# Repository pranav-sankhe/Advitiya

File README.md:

# Advitiya| Electrical Subsystem| [Pranav Sankhe](https://sabsathai.github.io/)

Hey! I am 3rd year Undergraduate at Electrical Engineering, IIT Bombay and a core member of [Electrical Subsystem](http://www.aero.iitb.ac.in/pratham/elecSS.php) of [Student Satellite Team, IIT Bombay](http://www.aero.iitb.ac.in/pratham/). **Advitiya** is the 2nd student satellite of IITB, technically advanced and efficient version of the 1st, Pratham. 

This is my repository where I maintain my codes related to Advitiya. 

</br>

If you want to contribute, you are most welcome :smiley: .Feel free to send a [pull request](https://help.github.com/articles/creating-a-pull-request/)

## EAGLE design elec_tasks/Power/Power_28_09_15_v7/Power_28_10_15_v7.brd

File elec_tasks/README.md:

# Electrical Subsystem Tasks

This contains the collection of all the codes written for tasks of electrical subsystem of Advitiya

- **Power** 
	Analysing the power boards of Pratham

- **Insystem Programming**
	The tasks involves programming a Atmega using another Atmega. 

- **UART Interrupts** 
	This task involved reading up on UART Transmit Interrupts and what specific applications do they cover

- **WatchDog Timer** 
	An implementation of WatchDog Timer in an Embedded System

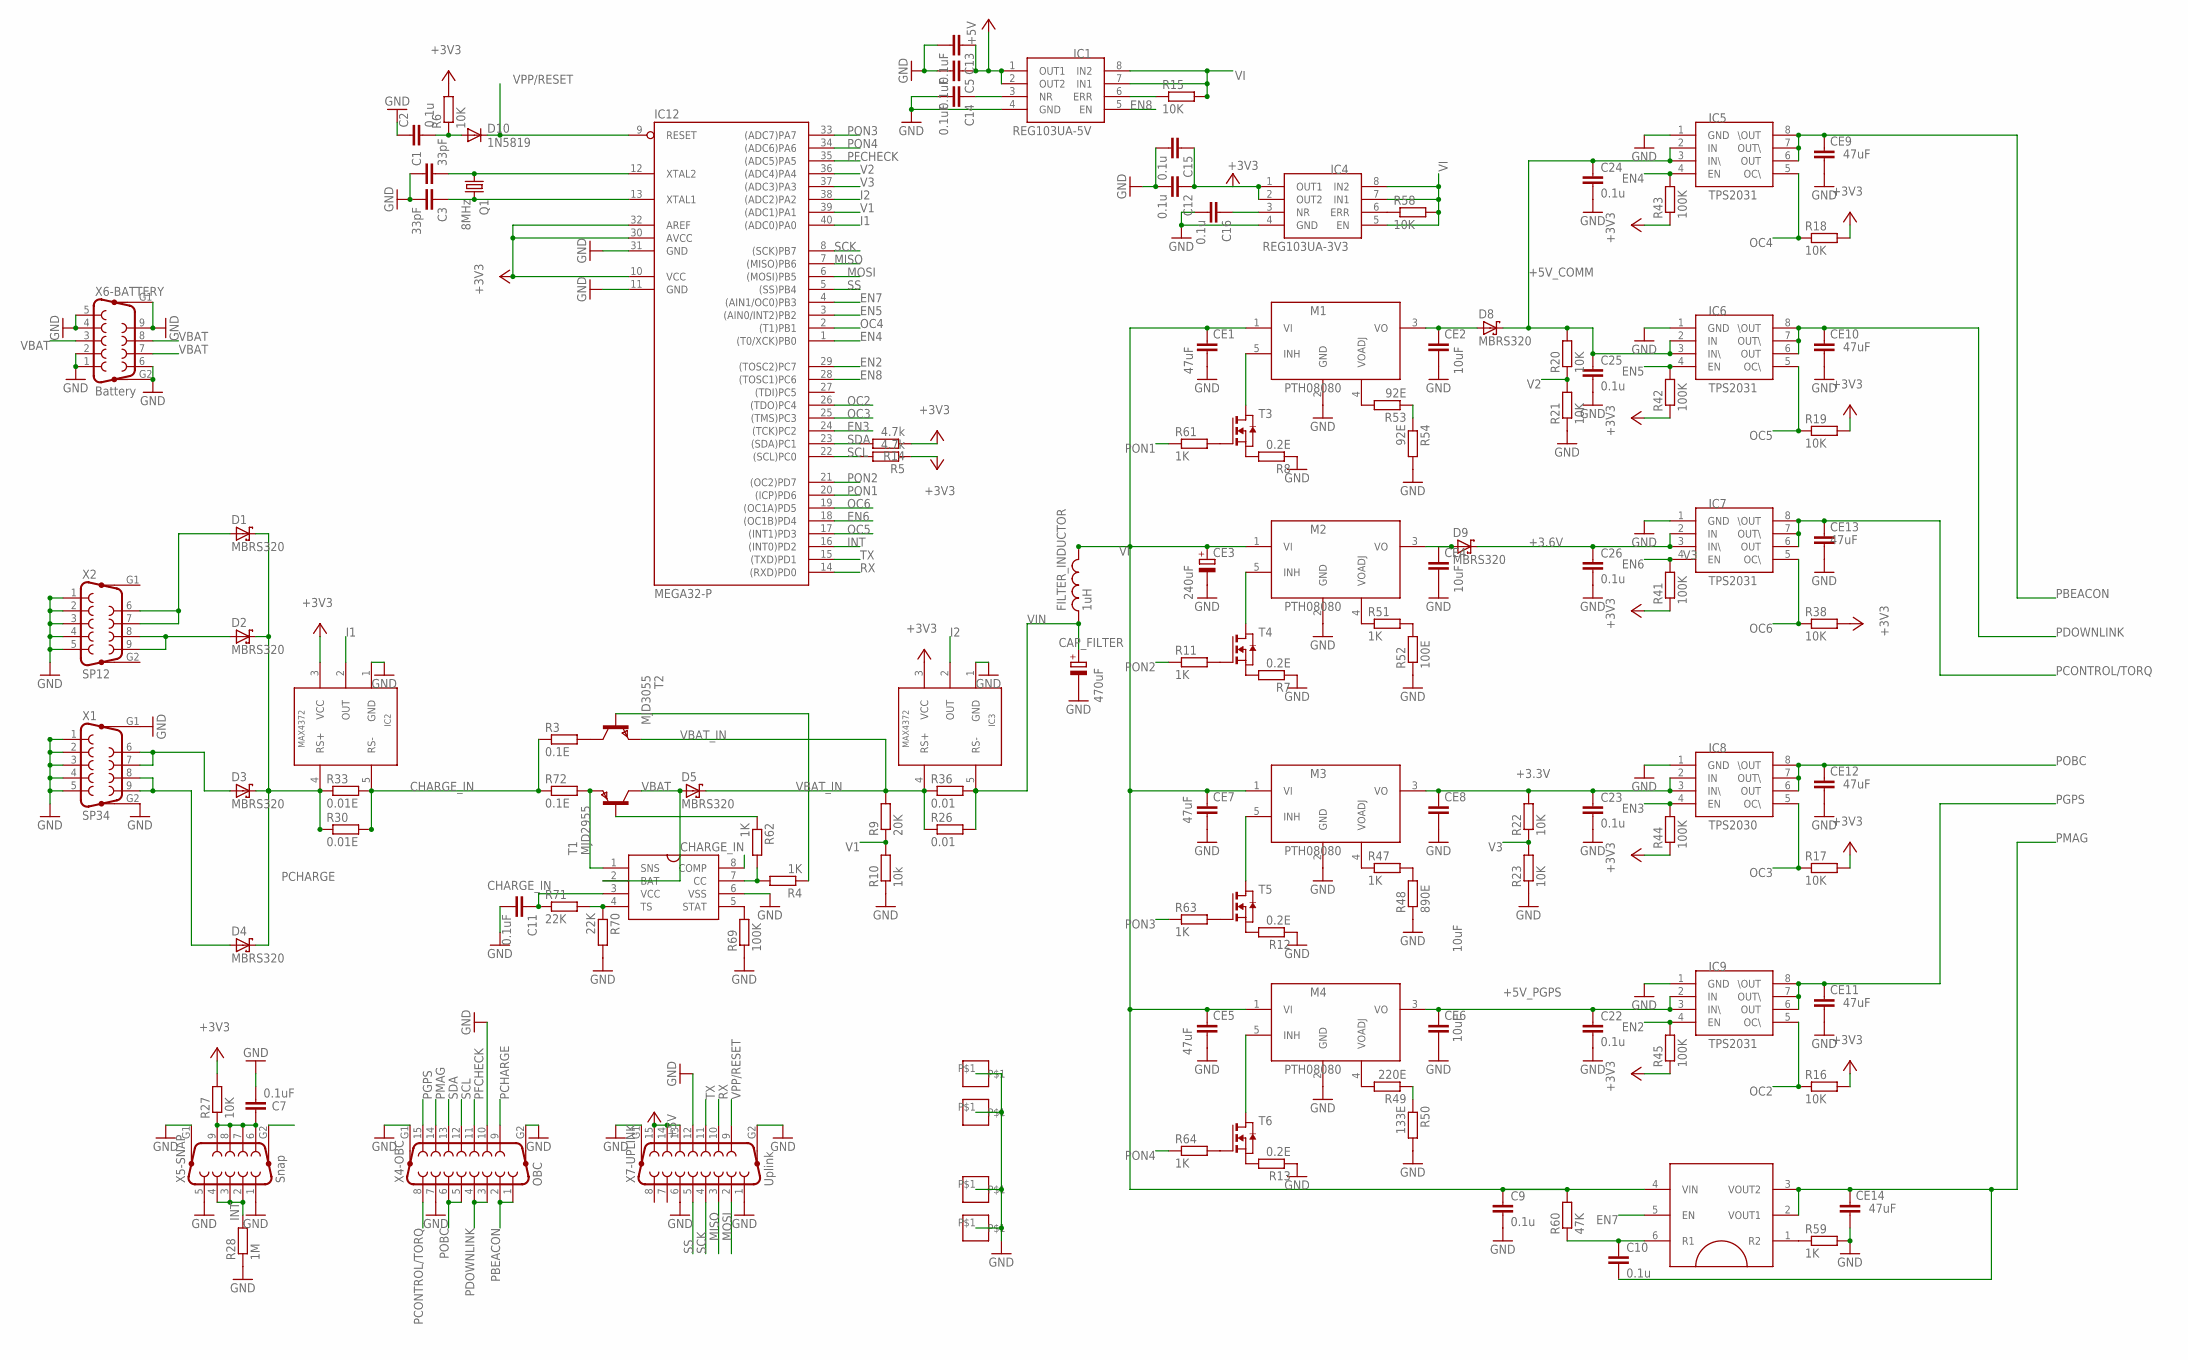
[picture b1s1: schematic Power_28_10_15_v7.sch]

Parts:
C1, C3: 33pF; C1206
C2, C9, C10, C12, C15, C16, C22, C23, C24, C25, C26: 0.1u; C1206
C5, C7, C11, C13, C14: 0.1uF; C1206
CAP_FILTER: 470uF; CAP-POL-T3
CE1, CE5, CE7, CE9, CE10, CE11, CE12, CE13, CE14: 47uF; C1206K
CE2, CE4, CE6, CE8: 10uF; C1206K
CE3: 240uF; CAP-POL-T2
D1, D2, D3, D4, D5, D8, D9: MBRS320; DIODE
D10: 1N5819; D-5
FILTER_INDUCTOR: 1uH; MSS1260
IC1: REG103UA-5V; SO8
IC2, IC3: MAX4372; SOT-23-5
IC4: REG103UA-3V3; SO8
IC5, IC6, IC7, IC9: TPS2031; SO-8
IC8: TPS2030; SO-8
IC10: FDC6324; SUPER-SOT-6
IC11: BO2057; SOIC-8
IC12: MEGA32-P; DIL40
M1, M2, M3, M4: PTH08080; DIP-05
Q1: 8MHz; HC49/S
R3, R72: 0.1E; R1206
R4, R11, R47, R51, R59, R61, R62, R63, R64: 1K; R1206
R5, R14: 4.7k; R1206
R6, R15, R16, R17, R18, R19, R20, R21, R22, R23, R27, R38, R58: 10K; R1206
R7, R8, R12, R13: 0.2E; R1206
R9: 20K; R1206
R10: 10k; R1206
R26, R36: 0.01; R1206
R28: 1M; R1206
R30, R33: 0.01E; R1206
R41, R42, R43, R44, R45, R69: 100K; R1206
R48: 890E; R1206
R49: 220E; R1206
R50: 133E; R1206
R52: 100E; R1206
R53, R54: 92E; R1206
R60: 47K; R1206
R70, R71: 22K; R1206
T1: MJD2955; DPAK-TO252
T2: MJD3055; DPAK-TO252
T3, T4, T5, T6: NMOSSOT23; SOT-23
U$4, U$16, U$18, U$19: MOUNT_SQ; MOUNT_10MM
X1: SP34; F09HP
X2: SP12; F09HP
X4-OBC: OBC; F15HP
X5-SNAP: Snap; F09HP
X6-BATTERY: Battery; F09HP
X7-UPLINK: Uplink; F15HP

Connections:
+3.3V: C23.1, CE8.1, IC8.2 (IN), IC8.3 (IN\), M3.3 (VO), R22.2
+3.6V: C26.1, D9.C, IC7.2 (IN), IC7.3 (IN\)
+3V3: C12.1, C15.1, IC2.3 (VCC), IC3.3 (VCC), IC4.1 (OUT1), IC4.2 (OUT2), IC12.10 (VCC), IC12.30 (AVCC), IC12.32 (AREF), R5.1, R6.2, R14.1, R16.2, R17.2, R18.2, R19.2, R27.2, R38.2, R41.1, R42.1, R43.1, R44.1, R45.1
+5V: C5.1, C13.1, IC1.1 (OUT1), IC1.2 (OUT2), X7-UPLINK.13, X7-UPLINK.14, X7-UPLINK.15
+5V_COMM: C24.1, C25.1, D8.C, IC5.2 (IN), IC5.3 (IN\), IC6.2 (IN), IC6.3 (IN\), R20.2
+5V_PGPS: C22.1, CE6.1, IC9.2 (IN), IC9.3 (IN\), M4.3 (VO)
CHARGE_IN: C11.1, IC2.5 (RS-), IC11.3 (VCC), IC11.8 (COMP), R3.1, R30.2, R33.2, R71.1, R72.1
EN2: IC9.4 (EN), IC12.29 ((TOSC2)PC7), R45.2
EN3: IC8.4 (EN), IC12.24 ((TCK)PC2), R44.2
EN4: IC5.4 (EN), IC12.1 ((T0/XCK)PB0), R43.2
EN5: IC6.4 (EN), IC12.3 ((AIN0/INT2)PB2), R42.2
EN6: IC7.4 (EN), IC12.18 ((OC1B)PD4), R41.2
EN7: IC10.5 (EN), IC12.4 ((AIN1/OC0)PB3)
EN8: IC1.5 (EN), IC12.28 ((TOSC1)PC6)
GND: C1.1, C2.1, C3.2, C5.2, C7.2, C9.2, C11.2, C12.2, C13.2, C14.2, C15.2, C16.2, C22.2, C23.2, C24.2, C25.2, C26.2, CAP_FILTER.P$2 (-), CE1.2, CE2.2, CE3.P$2 (-), CE4.2, CE5.2, CE6.2, CE7.2, CE8.2, CE9.2, CE10.2, CE11.2, CE12.2, CE13.2, CE14.2, IC1.4 (GND), IC2.1 (GND), IC3.1 (GND), IC4.4 (GND), IC5.1 (GND), IC6.1 (GND), IC7.1 (GND), IC8.1 (GND), IC9.1 (GND), IC11.6 (VSS), IC12.11 (GND), IC12.31 (GND), M1.2 (GND), M2.2 (GND), M3.2 (GND), M4.2 (GND), R7.1, R8.1, R10.1, R12.1, R13.1, R21.1, R23.1, R28.1, R48.1, R50.2, R52.1, R54.2, R59.2, R69.1, R70.2, U$4.P$1, U$16.P$1, U$18.P$1, U$19.P$1, X1.1, X1.2, X1.3, X1.4, X1.5, X1.G1, X1.G2, X2.1, X2.2, X2.3, X2.4, X2.5, X4-OBC.7, X4-OBC.10, X4-OBC.G1, X4-OBC.G2, X5-SNAP.1, X5-SNAP.5, X5-SNAP.G1, X5-SNAP.G2, X6-BATTERY.1, X6-BATTERY.2, X6-BATTERY.4, X6-BATTERY.5, X6-BATTERY.6, X6-BATTERY.9, X6-BATTERY.G1, X6-BATTERY.G2, X7-UPLINK.1, X7-UPLINK.6, X7-UPLINK.12, X7-UPLINK.G1, X7-UPLINK.G2
I1: IC2.2 (OUT), IC12.40 ((ADC0)PA0)
I2: IC3.2 (OUT), IC12.38 ((ADC2)PA2)
INT: IC12.16 ((INT0)PD2), R28.2, X5-SNAP.2, X5-SNAP.3, X5-SNAP.4
MISO: IC12.7 ((MISO)PB6), X7-UPLINK.3
MOSI: IC12.6 ((MOSI)PB5), X7-UPLINK.2
unnamed: D3.A, X1.6, X1.7
unnamed: D2.A, X2.8, X2.9
unnamed: C7.1, R27.1, X5-SNAP.6, X5-SNAP.7, X5-SNAP.8, X5-SNAP.9
unnamed: C16.1, IC4.3 (NR)
unnamed: C14.1, IC1.3 (NR)
unnamed: C2.2, D10.A, R6.1
unnamed: IC4.6 (ERR), R58.1
unnamed: R3.2, T2.2 (C)
unnamed: CE2.1, D8.A, M1.3 (VO)
unnamed: CE4.1, D9.A, M2.3 (VO)
unnamed: R4.1, T2.1 (B)
unnamed: C10.1, IC10.6 (R1), R60.1
unnamed: IC1.6 (ERR), R15.1
unnamed: M1.5 (INH), T3.1 (D)
unnamed: M3.5 (INH), T5.1 (D)
unnamed: M4.5 (INH), T6.1 (D)
unnamed: R7.2, T4.2 (S)
unnamed: C3.1, IC12.13 (XTAL1), Q1.2
unnamed: R61.2, T3.3 (G)
unnamed: R8.2, T3.2 (S)
unnamed: R11.2, T4.3 (G)
unnamed: D4.A, X1.8, X1.9
unnamed: IC10.1 (R2), R59.1
unnamed: C1.2, IC12.12 (XTAL2), Q1.1
unnamed: R63.2, T5.3 (G)
unnamed: R12.2, T5.2 (S)
unnamed: R64.2, T6.3 (G)
unnamed: R13.2, T6.2 (S)
unnamed: M2.5 (INH), T4.1 (D)
unnamed: D1.A, X2.6, X2.7
unnamed: M3.4 (VOADJ), R47.1
unnamed: R47.2, R48.2
unnamed: M4.4 (VOADJ), R49.2
unnamed: R49.1, R50.1
unnamed: M2.4 (VOADJ), R51.1
unnamed: R51.2, R52.2
unnamed: M1.4 (VOADJ), R53.2
unnamed: R53.1, R54.1
unnamed: R62.1, T1.1 (B)
unnamed: IC11.5 (STAT), R69.2
unnamed: IC11.4 (TS), R70.1, R71.2
unnamed: IC11.1 (SNS), R72.2, T1.3 (E)
unnamed: IC11.7 (CC), R4.2, R62.2
OC2: IC9.5 (OC\), IC12.26 ((TDO)PC4), R16.1
OC3: IC8.5 (OC\), IC12.25 ((TMS)PC3), R17.1
OC4: IC5.5 (OC\), IC12.2 ((T1)PB1), R18.1
OC5: IC6.5 (OC\), IC12.17 ((INT1)PD3), R19.1
OC6: IC7.5 (OC\), IC12.19 ((OC1A)PD5), R38.1
PBEACON: CE9.1, IC5.6 (OUT), IC5.7 (OUT\), IC5.8 (\OUT), X4-OBC.1, X4-OBC.2
PCHARGE: D1.C, D2.C, D3.C, D4.C, IC2.4 (RS+), R30.1, R33.1, X4-OBC.9
PCONTROL/TORQ: CE13.1, IC7.6 (OUT), IC7.7 (OUT\), IC7.8 (\OUT), X4-OBC.8
PDOWNLINK: CE10.1, IC6.6 (OUT), IC6.7 (OUT\), IC6.8 (\OUT), X4-OBC.3, X4-OBC.4
PFCHECK: IC12.35 ((ADC5)PA5), X4-OBC.11
PGPS: CE11.1, IC9.6 (OUT), IC9.7 (OUT\), IC9.8 (\OUT), X4-OBC.15
PMAG: C10.2, CE14.1, IC10.2 (VOUT1), IC10.3 (VOUT2), X4-OBC.14
POBC: CE12.1, IC8.6 (OUT), IC8.7 (OUT\), IC8.8 (\OUT), X4-OBC.5, X4-OBC.6
PON1: IC12.20 ((ICP)PD6), R61.1
PON2: IC12.21 ((OC2)PD7), R11.1
PON3: IC12.33 ((ADC7)PA7), R63.1
PON4: IC12.34 ((ADC6)PA6), R64.1
RX: IC12.14 ((RXD)PD0), X7-UPLINK.10
SCK: IC12.8 ((SCK)PB7), X7-UPLINK.4
SCL: IC12.22 ((SCL)PC0), R5.2, X4-OBC.12
SDA: IC12.23 ((SDA)PC1), R14.2, X4-OBC.13
SS: IC12.5 ((SS)PB4), X7-UPLINK.5
TX: IC12.15 ((TXD)PD1), X7-UPLINK.11
V1: IC12.39 ((ADC1)PA1), R9.1, R10.2
V2: IC12.36 ((ADC4)PA4), R20.1, R21.2
V3: IC12.37 ((ADC3)PA3), R22.1, R23.2
VBAT: D5.A, IC11.2 (BAT), T1.2 (C), X6-BATTERY.3, X6-BATTERY.7, X6-BATTERY.8
VBAT_IN: D5.C, IC3.4 (RS+), R9.2, R26.1, R36.1, T2.3 (E)
VI: C9.1, CE1.1, CE3.P$1 (+), CE5.1, CE7.1, FILTER_INDUCTOR.P$1, IC1.7 (IN1), IC1.8 (IN2), IC4.5 (EN), IC4.7 (IN1), IC4.8 (IN2), IC10.4 (VIN), M1.1 (VI), M2.1 (VI), M3.1 (VI), M4.1 (VI), R15.2, R58.2, R60.2
VIN: CAP_FILTER.P$1 (+), FILTER_INDUCTOR.P$2, IC3.5 (RS-), R26.2, R36.2
VPP/RESET: D10.C, IC12.9 (RESET), X7-UPLINK.9

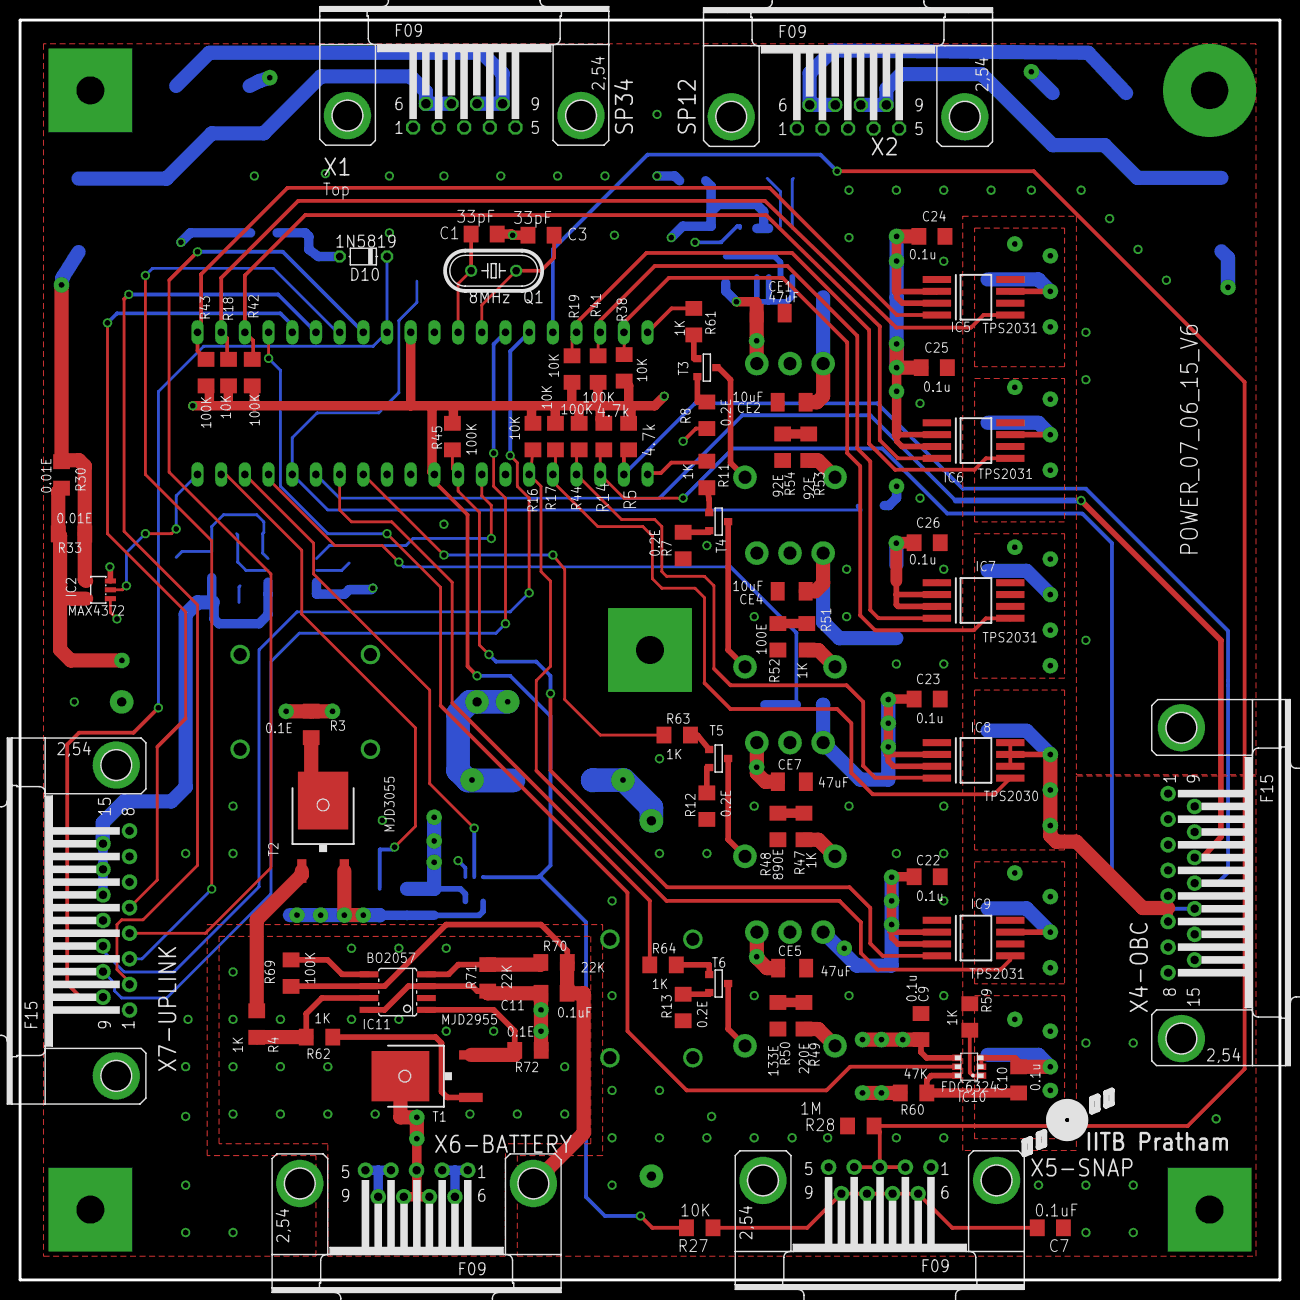
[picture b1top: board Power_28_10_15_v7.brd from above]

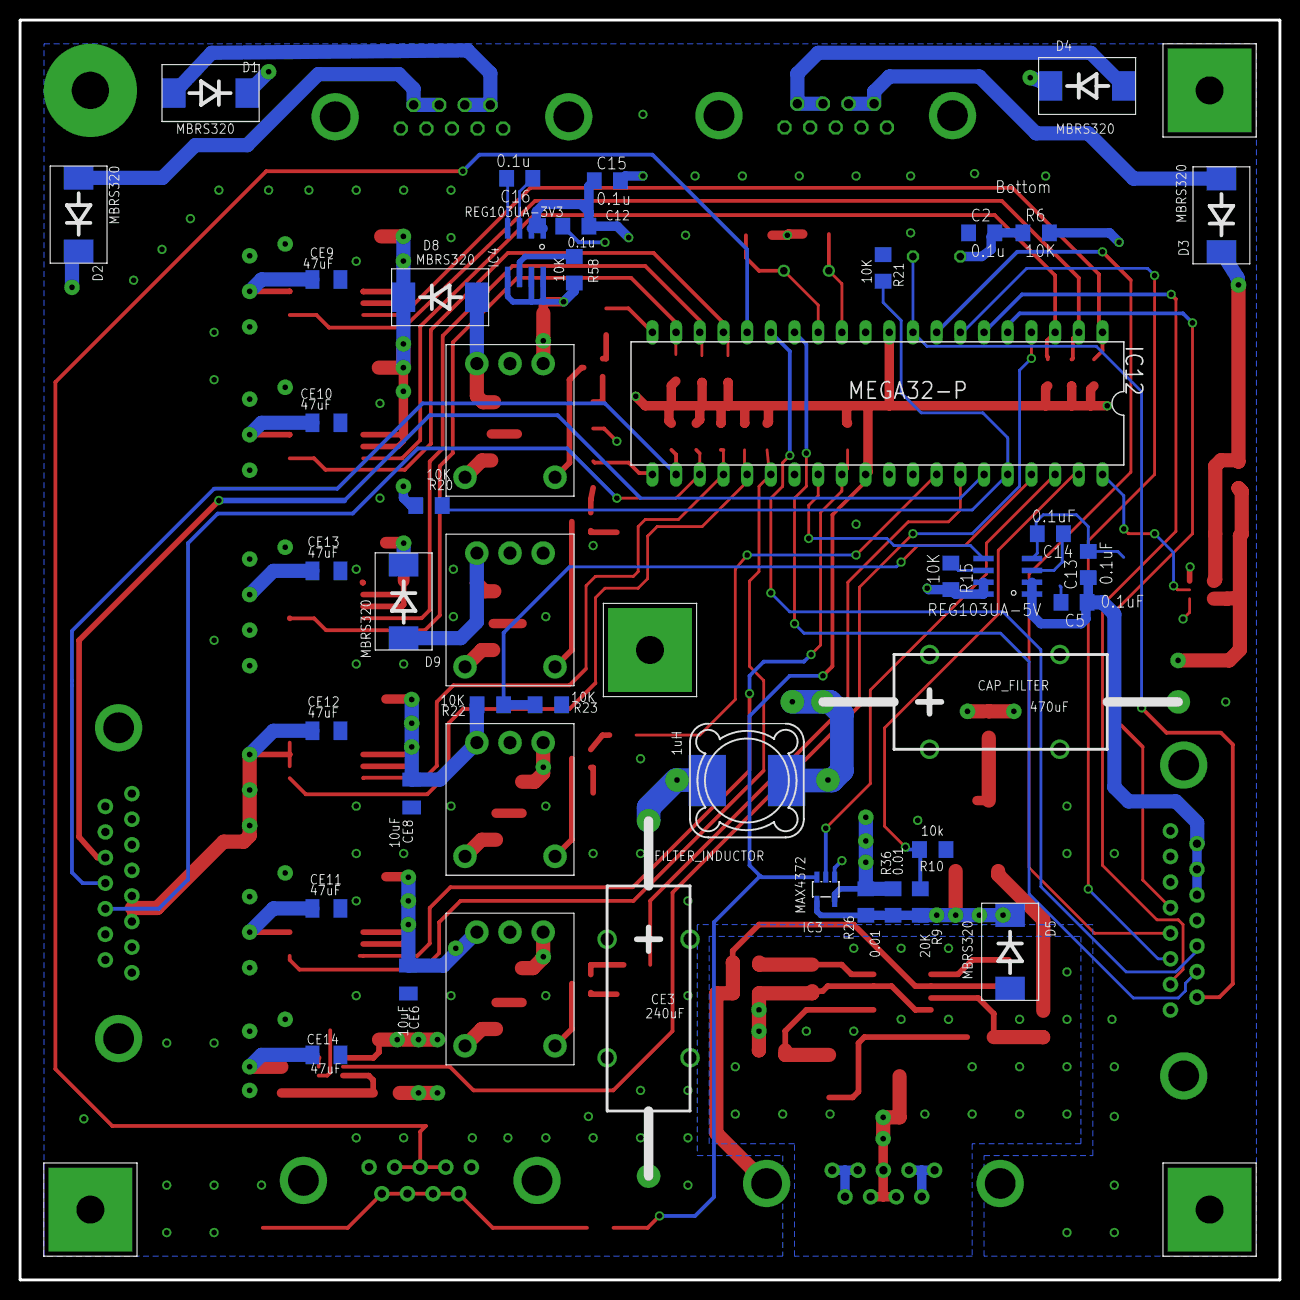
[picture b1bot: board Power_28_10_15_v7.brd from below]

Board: 2 copper layers, 135.1 x 135.1 mm, 127 parts (48 on the bottom side), 94 nets.

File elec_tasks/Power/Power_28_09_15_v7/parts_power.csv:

C2,0.1u,C1206,rcl
C9,0.1u,C1206,rcl
C10,0.1u,C1206,rcl
C12,0.1u,C1206,rcl
C15,0.1u,C1206,rcl
C16,0.1u,C1206,rcl
C22,0.1u,C1206,rcl
C23,0.1u,C1206,rcl
C24,0.1u,C1206,rcl
C25,0.1u,C1206,rcl
C26,0.1u,C1206,rcl
C5,0.1uF,C1206,rcl
C7,0.1uF,C1206,rcl
C11,0.1uF,C1206,rcl
C13,0.1uF,C1206,rcl
C14,0.1uF,C1206,rcl
C1,33pF,C1206,rcl
C3,33pF,C1206,rcl
CE2,10uF,C1206K,rcl
CE4,10uF,C1206K,rcl
CE6,10uF,C1206K,rcl
CE8,10uF,C1206K,rcl
CE1,47uF,C1206K,rcl
CE5,47uF,C1206K,rcl
CE7,47uF,C1206K,rcl
CE9,47uF,C1206K,rcl
CE10,47uF,C1206K,rcl
CE11,47uF,C1206K,rcl
CE12,47uF,C1206K,rcl
CE13,47uF,C1206K,rcl
CE14,47uF,C1206K,rcl
CE3,240uF,CAP-POL-T2,satellite
CAP_FILTER,470uF,CAP-POL-T3,satellite
D10,1N5819,D-5,diode
IC12,MEGA32-P,DIL40,atmel
D1,MBRS320,DIODE,satellite
D2,MBRS320,DIODE,satellite
D3,MBRS320,DIODE,satellite
D4,MBRS320,DIODE,satellite
D5,MBRS320,DIODE,satellite
D8,MBRS320,DIODE,satellite
D9,MBRS320,DIODE,satellite
M1,PTH08080,DIP-05,satellite
M2,PTH08080,DIP-05,satellite
M3,PTH08080,DIP-05,satellite
M4,PTH08080,DIP-05,satellite
T1,MJD2955,DPAK-TO252,satellite
T2,MJD3055,DPAK-TO252,satellite
X6-BATTERY,Battery,F09HP,satellite
X5-SNAP,Snap,F09HP,satellite
X2,SP12,F09HP,con-subd
X1,SP34,F09HP,con-subd
X4-OBC,OBC,F15HP,satellite
X7-UPLINK,Uplink,F15HP,satellite
Q1,8MHz,HC49/S,crystal
U$4,MOUNT_SQ,MOUNT_10MM,satellite
U$16,MOUNT_SQ,MOUNT_10MM,satellite
U$18,MOUNT_SQ,MOUNT_10MM,satellite
U$19,MOUNT_SQ,MOUNT_10MM,satellite
FILTER_INDUCT,OR 1uH,MSS1260,inductor-coilcraft(2)
R26,0.01,R1206,rcl
R36,0.01,R1206,rcl
R30,0.01E,R1206,rcl
R33,0.01E,R1206,rcl
R3,0.1E,R1206,rcl
R72,0.1E,R1206,rcl
R7,0.2E,R1206,rcl
R8,0.2E,R1206,rcl
R12,0.2E,R1206,rcl
R13,0.2E,R1206,rcl
R52,100E,R1206,rcl
R41,100K,R1206,rcl
R42,100K,R1206,rcl
R43,100K,R1206,rcl
R44,100K,R1206,rcl
R45,100K,R1206,rcl
R69,100K,R1206,rcl
R6,10K,R1206,rcl
R10,10k,R1206,rcl
R15,10K,R1206,rcl
R16,10K,R1206,rcl
R17,10K,R1206,rcl
R18,10K,R1206,rcl
R19,10K,R1206,rcl
R20,10K,R1206,rcl
R21,10K,R1206,rcl
R22,10K,R1206,rcl
R23,10K,R1206,rcl
R27,10K,R1206,rcl
R38,10K,R1206,rcl
R58,10K,R1206,rcl
R50,133E,R1206,rcl
R4,1K,R1206,rcl
R11,1K,R1206,rcl
R47,1K,R1206,rcl
R51,1K,R1206,rcl
R59,1K,R1206,rcl
R61,1K,R1206,rcl
R62,1K,R1206,rcl
R63,1K,R1206,rcl
R64,1K,R1206,rcl
R28,1M,R1206,rcl
R9,20K,R1206,rcl
R49,220E,R1206,rcl
R70,22K,R1206,rcl
R71,22K,R1206,rcl
R5,4.7k,R1206,rcl
R14,4.7k,R1206,rcl
R60,47K,R1206,rcl
R48,890E,R1206,rcl
R53,92E,R1206,rcl
R54,92E,R1206,rcl
IC4,REG103UA-3V3,SO8,satellite
IC1,REG103UA-5V,SO8,satellite
IC8,TPS2030,SO-8,satellite
IC5,TPS2031,SO-8,satellite
IC6,TPS2031,SO-8,satellite
IC7,TPS2031,SO-8,satellite
IC9,TPS2031,SO-8,satellite
IC11,BO2057,SOIC-8,satellite
T3,,SOT-23,zetex
T4,,SOT-23,zetex
T5,,SOT-23,zetex
T6,,SOT-23,zetex
IC2,MAX4372,SOT-23-5,satellite
IC3,MAX4372,SOT-23-5,satellite
IC10,FDC6324,SUPER-SOT-6,satellite
Partlist,,,

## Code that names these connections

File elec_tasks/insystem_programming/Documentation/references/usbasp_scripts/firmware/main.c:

/*
 * USBasp - USB in-circuit programmer for Atmel AVR controllers
 *
 * Thomas Fischl <tfischl@gmx.de>
 *
 * License........: GNU GPL v2 (see Readme.txt)
 * Target.........: ATMega8 at 12 MHz
 * Creation Date..: 2005-02-20
 * Last change....: 2009-02-28
 *
 * PC2 SCK speed option.
 * GND  -> slow (8khz SCK),
 * open -> software set speed (default is 375kHz SCK)
 */

#include <avr/io.h>
#include <avr/interrupt.h>
#include <avr/pgmspace.h>
#include <avr/wdt.h>

#include "usbasp.h"
#include "usbdrv.h"
#include "isp.h"
#include "clock.h"
#include "tpi.h"
#include "tpi_defs.h"

static uchar replyBuffer[8];

static uchar prog_state = PROG_STATE_IDLE;
static uchar prog_sck = USBASP_ISP_SCK_AUTO;

static uchar prog_address_newmode = 0;
static unsigned long prog_address;
static unsigned int prog_nbytes = 0;
static unsigned int prog_pagesize;
static uchar prog_blockflags;
static uchar prog_pagecounter;

uchar usbFunctionSetup(uchar data[8]) {

	uchar len = 0;

	if (data[1] == USBASP_FUNC_CONNECT) {

		/* set SCK speed */
		if ((PINC & (1 << PC2)) == 0) {
			ispSetSCKOption(USBASP_ISP_SCK_8);
		} else {
			ispSetSCKOption(prog_sck);
		}

		/* set compatibility mode of address delivering */
		prog_address_newmode = 0;

		ledRedOn();
		ispConnect();

	} else if (data[1] == USBASP_FUNC_DISCONNECT) {
		ispDisconnect();
		ledRedOff();

	} else if (data[1] == USBASP_FUNC_TRANSMIT) {
		replyBuffer[0] = ispTransmit(data[2]);
		replyBuffer[1] = ispTransmit(data[3]);
		replyBuffer[2] = ispTransmit(data[4]);
		replyBuffer[3] = ispTransmit(data[5]);
		len = 4;

	} else if (data[1] == USBASP_FUNC_READFLASH) {

		if (!prog_address_newmode)
			prog_address = (data[3] << 8) | data[2];

		prog_nbytes = (data[7] << 8) | data[6];
		prog_state = PROG_STATE_READFLASH;
		len = 0xff; /* multiple in */

	} else if (data[1] == USBASP_FUNC_READEEPROM) {

		if (!prog_address_newmode)
			prog_address = (data[3] << 8) | data[2];

		prog_nbytes = (data[7] << 8) | data[6];
		prog_state = PROG_STATE_READEEPROM;
		len = 0xff; /* multiple in */

	} else if (data[1] == USBASP_FUNC_ENABLEPROG) {
		replyBuffer[0] = ispEnterProgrammingMode();
		len = 1;

	} else if (data[1] == USBASP_FUNC_WRITEFLASH) {

		if (!prog_address_newmode)
			prog_address = (data[3] << 8) | data[2];

		prog_pagesize = data[4];
		prog_blockflags = data[5] & 0x0F;
		prog_pagesize += (((unsigned int) data[5] & 0xF0) << 4);
		if (prog_blockflags & PROG_BLOCKFLAG_FIRST) {
			prog_pagecounter = prog_pagesize;
		}
		prog_nbytes = (data[7] << 8) | data[6];
		prog_state = PROG_STATE_WRITEFLASH;
		len = 0xff; /* multiple out */

	} else if (data[1] == USBASP_FUNC_WRITEEEPROM) {

		if (!prog_address_newmode)
			prog_address = (data[3] << 8) | data[2];

		prog_pagesize = 0;
		prog_blockflags = 0;
		prog_nbytes = (data[7] << 8) | data[6];
		prog_state = PROG_STATE_WRITEEEPROM;
		len = 0xff; /* multiple out */

	} else if (data[1] == USBASP_FUNC_SETLONGADDRESS) {

		/* set new mode of address delivering (ignore address delivered in commands) */
		prog_address_newmode = 1;
		/* set new address */
		prog_address = *((unsigned long*) &data[2]);

	} else if (data[1] == USBASP_FUNC_SETISPSCK) {

		/* set sck option */
		prog_sck = data[2];
		replyBuffer[0] = 0;
		len = 1;

	} else if (data[1] == USBASP_FUNC_TPI_CONNECT) {
		tpi_dly_cnt = data[2] | (data[3] << 8);

		/* RST high */
		ISP_OUT |= (1 << ISP_RST);
		ISP_DDR |= (1 << ISP_RST);

		clockWait(3);

		/* RST low */
		ISP_OUT &= ~(1 << ISP_RST);
		ledRedOn();

		clockWait(16);
		tpi_init();
	
	} else if (data[1] == USBASP_FUNC_TPI_DISCONNECT) {

		tpi_send_byte(TPI_OP_SSTCS(TPISR));
		tpi_send_byte(0);

		clockWait(10);

		/* pulse RST */
		ISP_OUT |= (1 << ISP_RST);
		clockWait(5);
		ISP_OUT &= ~(1 << ISP_RST);
		clockWait(5);

		/* set all ISP pins inputs */
		ISP_DDR &= ~((1 << ISP_RST) | (1 << ISP_SCK) | (1 << ISP_MOSI));
		/* switch pullups off */
		ISP_OUT &= ~((1 << ISP_RST) | (1 << ISP_SCK) | (1 << ISP_MOSI));

		ledRedOff();
	
	} else if (data[1] == USBASP_FUNC_TPI_RAWREAD) {
		replyBuffer[0] = tpi_recv_byte();
		len = 1;
	
	} else if (data[1] == USBASP_FUNC_TPI_RAWWRITE) {
		tpi_send_byte(data[2]);
	
	} else if (data[1] == USBASP_FUNC_TPI_READBLOCK) {
		prog_address = (data[3] << 8) | data[2];
		prog_nbytes = (data[7] << 8) | data[6];
		prog_state = PROG_STATE_TPI_READ;
		len = 0xff; /* multiple in */
	
	} else if (data[1] == USBASP_FUNC_TPI_WRITEBLOCK) {
		prog_address = (data[3] << 8) | data[2];
		prog_nbytes = (data[7] << 8) | data[6];
		prog_state = PROG_STATE_TPI_WRITE;
		len = 0xff; /* multiple out */
	
	} else if (data[1] == USBASP_FUNC_GETCAPABILITIES) {
		replyBuffer[0] = USBASP_CAP_0_TPI;
		replyBuffer[1] = 0;
		replyBuffer[2] = 0;
		replyBuffer[3] = 0;
		len = 4;
	}

	usbMsgPtr = replyBuffer;

	return len;
}

uchar usbFunctionRead(uchar *data, uchar len) {

	uchar i;

	/* check if programmer is in correct read state */
	if ((prog_state != PROG_STATE_READFLASH) && (prog_state
			!= PROG_STATE_READEEPROM) && (prog_state != PROG_STATE_TPI_READ)) {
		return 0xff;
	}

	/* fill packet TPI mode */
	if(prog_state == PROG_STATE_TPI_READ)
	{
		tpi_read_block(prog_address, data, len);
		prog_address += len;
		return len;
	}

	/* fill packet ISP mode */
	for (i = 0; i < len; i++) {
		if (prog_state == PROG_STATE_READFLASH) {
			data[i] = ispReadFlash(prog_address);
		} else {
			data[i] = ispReadEEPROM(prog_address);
		}
		prog_address++;
	}

	/* last packet? */
	if (len < 8) {
		prog_state = PROG_STATE_IDLE;
	}

	return len;
}

uchar usbFunctionWrite(uchar *data, uchar len) {

	uchar retVal = 0;
	uchar i;

	/* check if programmer is in correct write state */
	if ((prog_state != PROG_STATE_WRITEFLASH) && (prog_state
			!= PROG_STATE_WRITEEEPROM) && (prog_state != PROG_STATE_TPI_WRITE)) {
		return 0xff;
	}

	if (prog_state == PROG_STATE_TPI_WRITE)
	{
		tpi_write_block(prog_address, data, len);
		prog_address += len;
		prog_nbytes -= len;
		if(prog_nbytes <= 0)
		{
			prog_state = PROG_STATE_IDLE;
			return 1;
		}
		return 0;
	}

	for (i = 0; i < len; i++) {

		if (prog_state == PROG_STATE_WRITEFLASH) {
			/* Flash */

			if (prog_pagesize == 0) {
				/* not paged */
				ispWriteFlash(prog_address, data[i], 1);
			} else {
				/* paged */
				ispWriteFlash(prog_address, data[i], 0);
				prog_pagecounter--;
				if (prog_pagecounter == 0) {
					ispFlushPage(prog_address, data[i]);
					prog_pagecounter = prog_pagesize;
				}
			}

		} else {
			/* EEPROM */
			ispWriteEEPROM(prog_address, data[i]);
		}

		prog_nbytes--;

		if (prog_nbytes == 0) {
			prog_state = PROG_STATE_IDLE;
			if ((prog_blockflags & PROG_BLOCKFLAG_LAST) && (prog_pagecounter
					!= prog_pagesize)) {

				/* last block and page flush pending, so flush it now */
				ispFlushPage(prog_address, data[i]);
			}

			retVal = 1; // Need to return 1 when no more data is to be received
		}

		prog_address++;
	}

	return retVal;
}

int main(void) {
	uchar i, j;

	/* no pullups on USB and ISP pins */
	PORTD = 0;
	PORTB = 0;
	/* all outputs except PD2 = INT0 */
	DDRD = ~(1 << 2);

	/* output SE0 for USB reset */
	DDRB = ~0;
	j = 0;
	/* USB Reset by device only required on Watchdog Reset */
	while (--j) {
		i = 0;
		/* delay >10ms for USB reset */
		while (--i)
			;
	}
	/* all USB and ISP pins inputs */
	DDRB = 0;

	/* all inputs except PC0, PC1 */
	DDRC = 0x03;
	PORTC = 0xfe;

	/* init timer */
	clockInit();

	/* main event loop */

	// usbInit();
	// sei();
	// for (;;) {
	// 	usbPoll();
	// }



	return 0;
}

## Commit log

2017-06-08 power circuit analysis
2017-06-08 references added
2017-06-08 images
2017-06-08 ham stuff
2017-06-08 advitiya mini project
2017-06-08 telescope paylaod
2017-06-08 C functions to access memory
2017-06-12 image added
2017-06-12 images of SPI Documentation
2017-06-12 SPI Documentation
2017-06-12 fixed syntatic errors
2017-06-20 Documentation
2017-06-20 avrdude source code files for usbasp
2017-06-20 usbasp source code
2017-06-20 makefil
2017-06-20 test
2017-06-20 restructured
2017-07-07 hex file format as specified by intel
2017-07-07 complete
2017-07-23 watchdog example
2017-09-27 added README file
2017-09-27 modified some files and added summary of Transmit Interrupts of UART
2017-09-28 added README
